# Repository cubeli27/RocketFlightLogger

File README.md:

# Rocket Flight Logger

## Overview

**Rocket Flight Logger** is developed for meassuring the acceleration of a pressurised rocket. The intial setup was d1-mini with esp8266 dev board and external IMU and battery connected with soldered wires. This project combines that into one board aiming to reduce all unnecessary weight.  

**Key Features:**
- 1S Bat connector on-board
- BMI088 IMU on-board
- Autoboot circuit simplified
- Minimal component count
- Programmer not part of PCBA

---

## Project Structure

| Folder | Description |
|--------|-------------|
| **CAD_files** | Contains `.stl` files  |
| **ECAD_files** | Contains PCB files |
| **Images** | ... |
| **Source_Code** | Firmware developed for this project |

---

## Wiring Diagram

How to program fresh boards.

---

## Final Results

PCB on the Rocket (pending)

---
## Future Work

Will be determined after more testing. 

## Author

Developed by **cubeli27**  
For questions or collaboration, feel free to reach out through GitHub.

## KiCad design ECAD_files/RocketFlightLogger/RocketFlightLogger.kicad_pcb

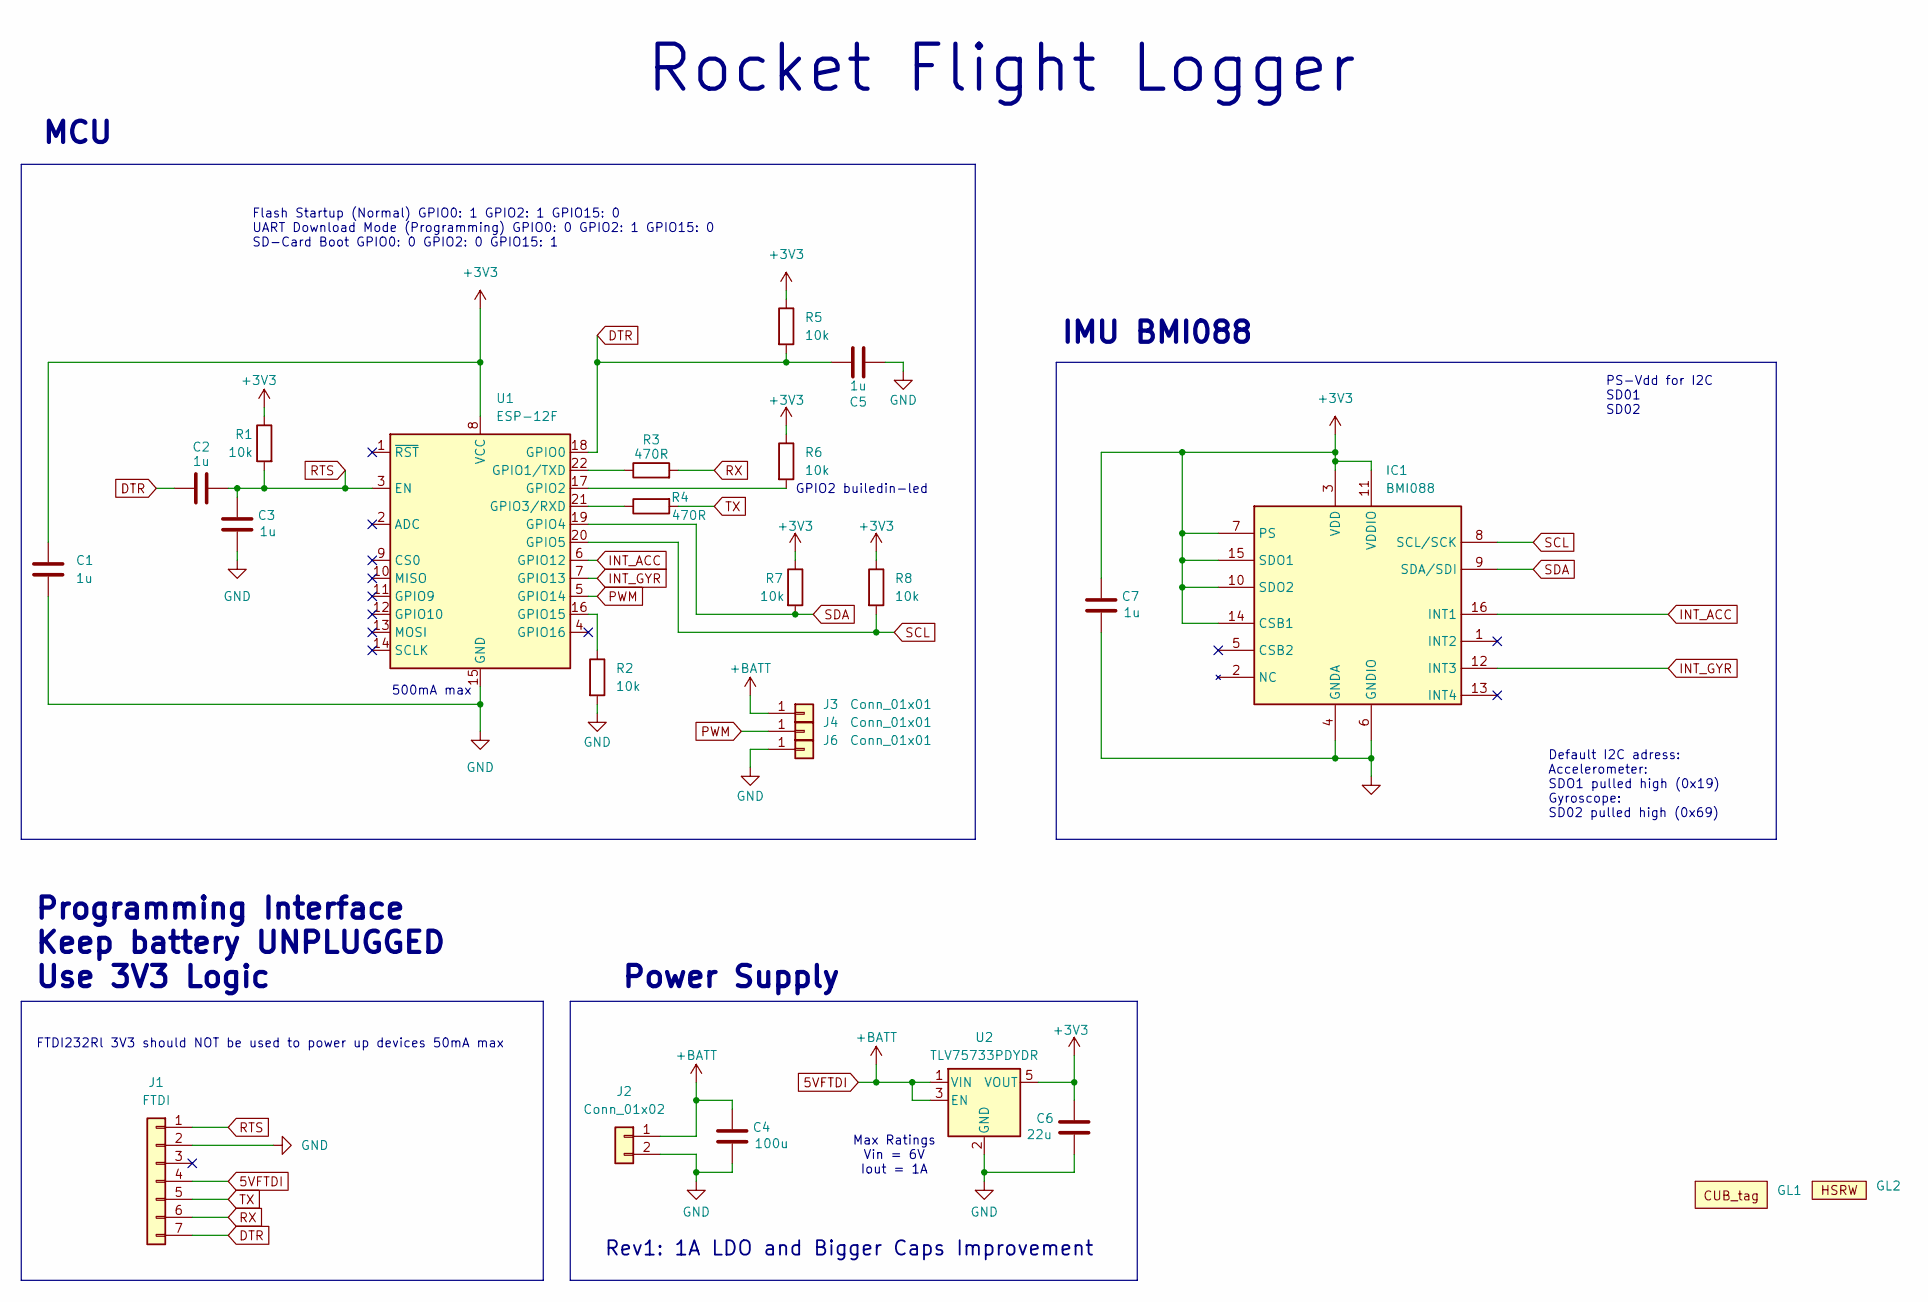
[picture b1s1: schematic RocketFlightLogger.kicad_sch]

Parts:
C1, C2, C3, C5, C7: 1u; C_0805_2012Metric_Pad1.18x1.45mm_HandSolder
C4: 100u; C_1206_3216Metric_Pad1.33x1.80mm_HandSolder
C6: 22u; C_0805_2012Metric_Pad1.18x1.45mm_HandSolder
GL1: CUB_tag
GL2: hsrwBS
IC1: BMI088; Mouser Part Number 262-BMI088
J1: FTDI; PinHeader_1x07_P2.54mm_Vertical
J2: Conn_01x02; JST_PH_S2B-PH-SM4-TB_1x02-1MP_P2.00mm_Horizontal
J3, J4, J6: Conn_01x01; TestPoint_Keystone_5015_Micro_Mini
R1, R2, R5, R6, R7, R8: 10k; R_0805_2012Metric_Pad1.20x1.40mm_HandSolder
R3, R4: 470R; R_0805_2012Metric_Pad1.20x1.40mm_HandSolder
U1: ESP-12F; ESP-12E
U2: TLV75733PDYDR; SOT-23-5

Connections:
5VFTDI: C4.1, J1.4, J2.1, J3.1, U2.1 (VIN), U2.3 (EN)
+3V3: C1.1, C6.1, C7.1, IC1.3 (VDD), IC1.7 (PS), IC1.10 (SDO2), IC1.11 (VDDIO), IC1.14 (CSB1), IC1.15 (SDO1), R1.1, R5.1, R6.1, R7.1, R8.1, U1.8 (VCC), U2.5 (VOUT)
DTR: C2.1, C5.1, J1.7, R5.2, U1.18 (GPIO0)
GND: C1.2, C3.2, C4.2, C5.2, C6.2, C7.2, IC1.4 (GNDA), IC1.6 (GNDIO), J1.2, J2.2, J6.1, R2.2, U1.15 (GND), U2.2 (GND)
INT_ACC: IC1.16 (INT1), U1.6 (GPIO12)
INT_GYR: IC1.12 (INT3), U1.7 (GPIO13)
unnamed: R3.1, U1.22 (GPIO1/TXD)
unnamed: R6.2, U1.17 (GPIO2)
unnamed: R4.1, U1.21 (GPIO3/RXD)
unnamed: R2.1, U1.16 (GPIO15)
PWM: J4.1, U1.5 (GPIO14)
RTS: C2.2, C3.1, J1.1, R1.2, U1.3 (EN)
RX: J1.6, R3.2
SCL: IC1.8 (SCL/SCK), R8.2, U1.20 (GPIO5)
SDA: IC1.9 (SDA/SDI), R7.2, U1.19 (GPIO4)
TX: J1.5, R4.2

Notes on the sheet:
Programming Interface Keep battery UNPLUGGED Use 3V3 Logic
GPIO2 builedin-led
Flash Startup (Normal) GPIO0: 1 GPIO2: 1 GPIO15: 0 UART Download Mode (Programming) GPIO0: 0 GPIO2: 1 GPIO15: 0 SD-Card Boot GPIO0: 0 GPIO2: 0 GPIO15: 1
Power Supply
PS-Vdd for I2C SD01 SD02
Max Ratings Vin = 6V Iout = 1A
FTDI232Rl 3V3 should NOT be used to power up devices 50mA max
Rev1: 1A LDO and Bigger Caps Improvement
Default I2C adress: Accelerometer: SDO1 pulled high (0x19) Gyroscope: SD02 pulled high (0x69)
MCU
IMU BMI088
500mA max
Rocket Flight Logger

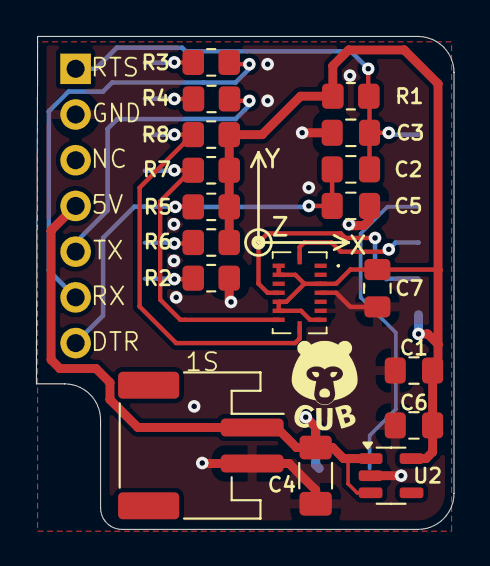
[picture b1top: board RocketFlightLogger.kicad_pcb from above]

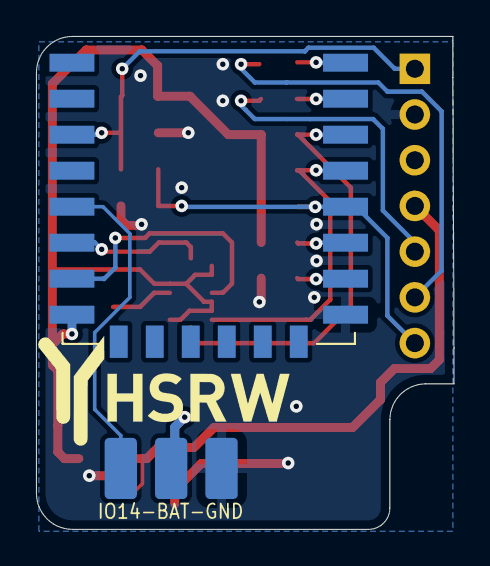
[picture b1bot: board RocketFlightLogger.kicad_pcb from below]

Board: 2 copper layers, 23.2 x 27.4 mm, 25 parts (4 on the bottom side), 16 nets.

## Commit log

2025-10-21 .jpg to .JPG
2025-10-21 Images
2025-10-21 typo
2025-10-22 Fix spelling errors in README overview
    Corrected spelling errors in the overview section.
2025-10-22 3d models added
2025-11-27 fix .gitignore file
